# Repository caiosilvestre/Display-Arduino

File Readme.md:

# Sensor de Temperatura com Display
## Projeto Utilizando arduino com Linguagem AVR

## Componentes:
- 1x Display de 4 segmentos.
- 8x Resistores.
- 1x Botão
- Barramento de pinos para acoplamento no arduino.
- 1x LM35.
- 1x Arduino uno.

## Objetivo do Projeto

- Ler o sinal do LM35 
- Converter o sinal em uma escalas de temperaturas
- Utilizar escalas de Temperatura Celsius, Fahrenheit e Kelvin
- Selecionar a escala que será exibida
- Exibir temperatura em tempo real

## Código

Programa requer [arduino.cc](https://www.arduino.cc/).

## Definir ações para as Portas

```sh
#define acende(Y,bit_x)(Y|=(1<<bit_x)) //ativa o bit x da variável Y (coloca em 1)
#define apaga(Y,bit_x)(Y&=~(1<<bit_x)) //limpa o bit x da variável Y (coloca em 0)
#define cpl_bit(Y,bit_x)(Y^=(1<<bit_x)) //troca o estado do bit x da variável Y
#define tst_bit(Y,bit_x)(Y&(1<<bit_x)) //testa o bit x da variável Y (retorna 0 ou 1)
#define BOT PB5
```

## Atribuir valores as variáveis

```sh
const int pinoPOT = A0;
int time = 5, escala = 10, pres = 0;
char  est = 'A';
const int LM35 = A0; // Define o pino que lera a saída do LM35
float temp = 0; // Variável que armazenará a temperatura medida
float VALOR  = 0;
```
## Definir as portas e os valores inicializados
```sh
void setup() {
  int i, s;
  DDRB =  0B00011111;
  DDRD =  0B11111100;
  PORTB = 0B11000001;
  PORTD = 0B11111100;
}
```
## Loop do programa
```sh
    void loop() {
  sete_seg((int)estado_botao());
}
```
## Digitos
- Criada uma matriz com 7 colunas representando os segmentos.
- 1 == HIGH , 0 == LOW.
- Matriz possue 13 linhas, representam um valor a ser exibido no display.
```sh
byte digits[13][7] = {
  { 1, 1, 1, 1, 1, 1, 0 }, // == Digito 0
  { 0, 1, 1, 0, 0, 0, 0 }, // == Digito 1
  { 1, 1, 0, 1, 1, 0, 1 }, // == Digito 2
  { 1, 1, 1, 1, 0, 0, 1 }, // == Digito 3
  { 0, 1, 1, 0, 0, 1, 1 }, // == Digito 4
  { 1, 0, 1, 1, 0, 1, 1 }, // == Digito 5
  { 1, 0, 1, 1, 1, 1, 1 }, // == Digito 6
  { 1, 1, 1, 0, 0, 0, 0 }, // == Digito 7
  { 1, 1, 1, 1, 1, 1, 1 }, // == Digito 8
  { 1, 1, 1, 0, 0, 1, 1 }, // == Digito 9
  { 1, 0, 0, 1, 1, 1, 0 }, // == Letra C
  { 1, 0, 0, 0, 1, 1, 1 }, // == Letra F
  { 1, 1, 1, 0, 1, 1, 1 }, // == Letra A
};  // 
```
## FUNÇÃO EXIBIÇÃO NO DISPLAY 
- Divide o numero inteiro em centena , dezena ,unidade.
- Assim podendo ser exibido de forma separada no display.
```sh
void sete_seg(int num) {
  int cem = (num % 1000) / 100;             /*Parte responsavel por transformar 1 numero em até 3 numeros, centena, Dezena, Unidade*/
  int dez = ((num % 1000) % 100) / 10;
  int uni = (((num % 1000) % 100) % 10);
  escolha_dig(cem);         /*Parte responsavel por determinar em que digito o valor será exibido*/
```
### Parte responsável atribuir cada valor a sua posição no display
- Chamando a função escolha_pos, responsavel por ativar a posição do display.
- Depois da um delay, em seguida chama outra função, responsável transformar o int em portas para display de 7  seguimentos.
```sh
  escolha_pos(0);
  _delay_ms(time);
  escolha_dig(dez);
  escolha_pos(1);
  _delay_ms(time);
  escolha_dig(uni);
  escolha_pos(2);
  _delay_ms(time);
  escolha_dig(escala);
  escolha_pos(3);
  _delay_ms(time);
  escolha_pos(4);
}
```
## Função responsável por selecionar os digitos
- Deixa apenas 1 digito ativo por vez
- Evitando assim exibir valores indesejáveis
```sh
void escolha_pos(int pos) {
  if (pos == 0)
  {
    apaga (PORTB, 1);
    acende(PORTB, 2);
    acende(PORTB, 3);
    acende(PORTB, 4);
  }
  if (pos == 1)
  {
    apaga(PORTB, 2);
    acende(PORTB, 1);
    acende(PORTB, 3);
    acende(PORTB, 4);
  }
  if (pos == 2)
  {
    apaga(PORTB, 3);
    acende(PORTB, 1);
    acende(PORTB, 2);
    acende(PORTB, 4);
  }
  if (pos == 3)
  {
    apaga(PORTB, 4);
    acende(PORTB, 2);
    acende(PORTB, 3);
    acende(PORTB, 1);
  }
}
```
## Traduz o valor int em sinal para o display
```sh
void escolha_dig(int num) {
  int i, j;
  for (i = 0; i < 7; i++)
  {
    if (i == 6 && digits[num][6] == 1)
      acende(PORTB, 0);
    else if (i == 6 && digits[num][6] == 0)
      apaga(PORTB, 0);
    else if (digits[num][i] == 1)
      acende(PORTD, i + 2);
    else
      apaga(PORTD, i + 2);
  }
}
```
## Convert o sinal do lm 35
```sh
float estado_botao()
{
  temp = analogRead(LM35); //RECEBENDO O VALOR INTEIRO
  temp = ((float)temp); // CONVERÇÃO PARA FLOAT
  temp = (temp * 5.0)/1023.0; // CONVERSAO PARA SINAL DE TENSAO
  temp = temp *100; // RESOLVENDO O VALOR
```
## Código para o botão conseguir selecionar a escala desejada
```sh
  switch (est) {
    case 'A':
      if (tst_bit(PINB, BOT))
      {
        pres = 1;
      }
      if (pres == 1 && !tst_bit(PINB, BOT)) {
        est = 'B';//  cesius
        escala = 11;
        pres = 0;
      }
      temp = temp;
      break;
    case 'B':
      if (tst_bit(PINB, BOT))
      {
        pres = 1;
      }
      temp = (temp * 9) / 5 + 32; //  F
      if (pres == 1 && !tst_bit(PINB, BOT)) {
        est = 'C';//  cesius
        escala = 12;
        pres = 0;
      }
      break;
    case 'C':
      if (tst_bit(PINB, BOT))
      {
        pres = 1;

      }
      temp = temp + 273;
      if (pres == 1 && !tst_bit(PINB, BOT)) {
        est = 'A';//  cesius
        escala = 10;
        pres = 0;
      }
      // K
      break;
    default:
      est = 'A';
      break;
  }
  return temp;
}
```

**Free Code!**

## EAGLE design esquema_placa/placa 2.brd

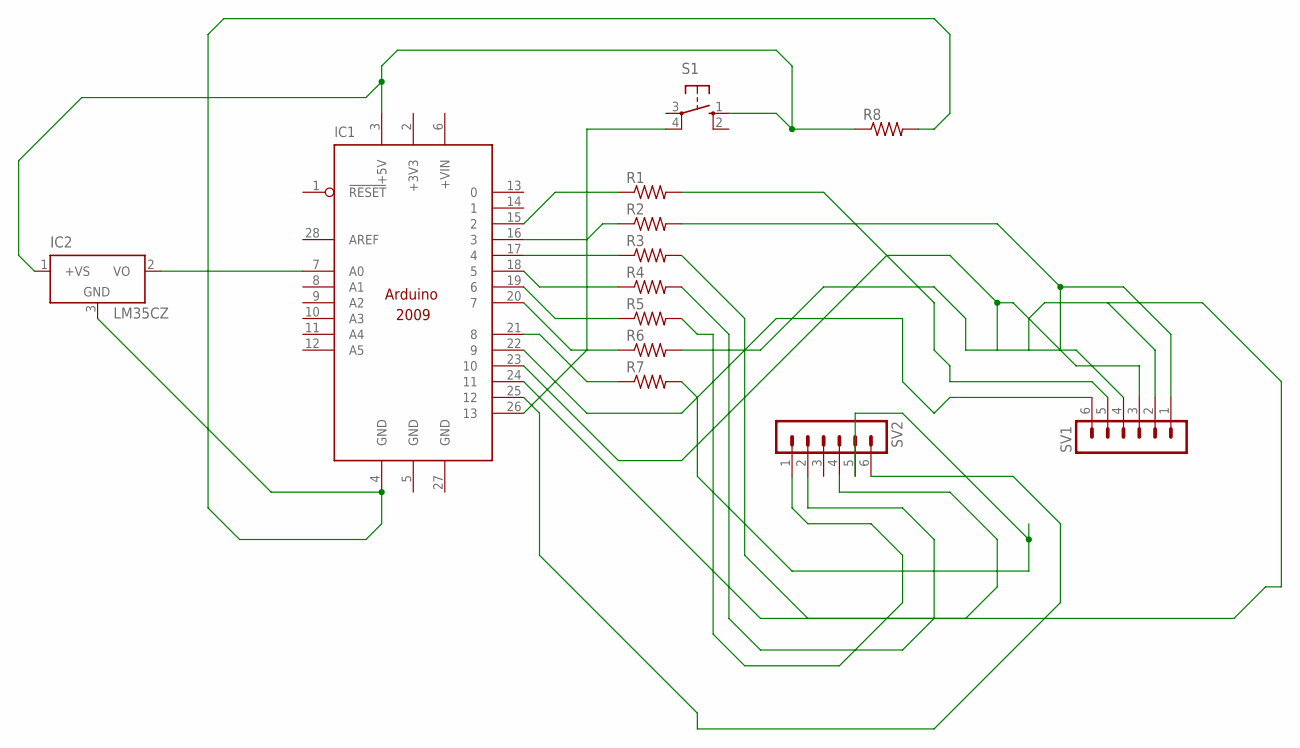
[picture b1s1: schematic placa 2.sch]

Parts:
IC1: ARDUINO2009_11; ARDUINO2009_1
IC2: LM35CZ; TO92
R1, R2, R3, R4, R5, R6, R7, R8: R-US_0207/15; 0207/15
S1: 10-XX; B3F-10XX
SV1, SV2: MA06-1

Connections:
+3V3: IC1.2 (+3V3)
GND: IC1.5 (GND), IC1.27 (GND)
unnamed: IC1.21 (8), R7.1
unnamed: IC1.20 (7), R6.1
unnamed: IC1.19 (6), R5.1
unnamed: IC1.18 (5), R4.1
unnamed: IC1.17 (4), R3.1
unnamed: IC1.16 (3), R2.1
unnamed: IC1.15 (2), R1.1
unnamed: R1.2, SV1.5
unnamed: R2.2, SV1.1
unnamed: R3.2, SV2.4
unnamed: R4.2, SV2.2
unnamed: R5.2, SV2.1
unnamed: R6.2, SV1.4
unnamed: R7.2, SV2.5
unnamed: IC1.22 (9), SV1.6
unnamed: IC1.23 (10), SV1.3
unnamed: IC1.24 (11), SV1.2
unnamed: IC1.25 (12), SV2.6
unnamed: IC1.3 (+5V), IC2.1 (+VS), R8.1, S1.1 (S)
unnamed: IC1.26 (13), S1.4 (P1)
unnamed: IC1.4 (GND), IC2.3 (GND), R8.2
unnamed: IC1.7 (A0), IC2.2 (VO)

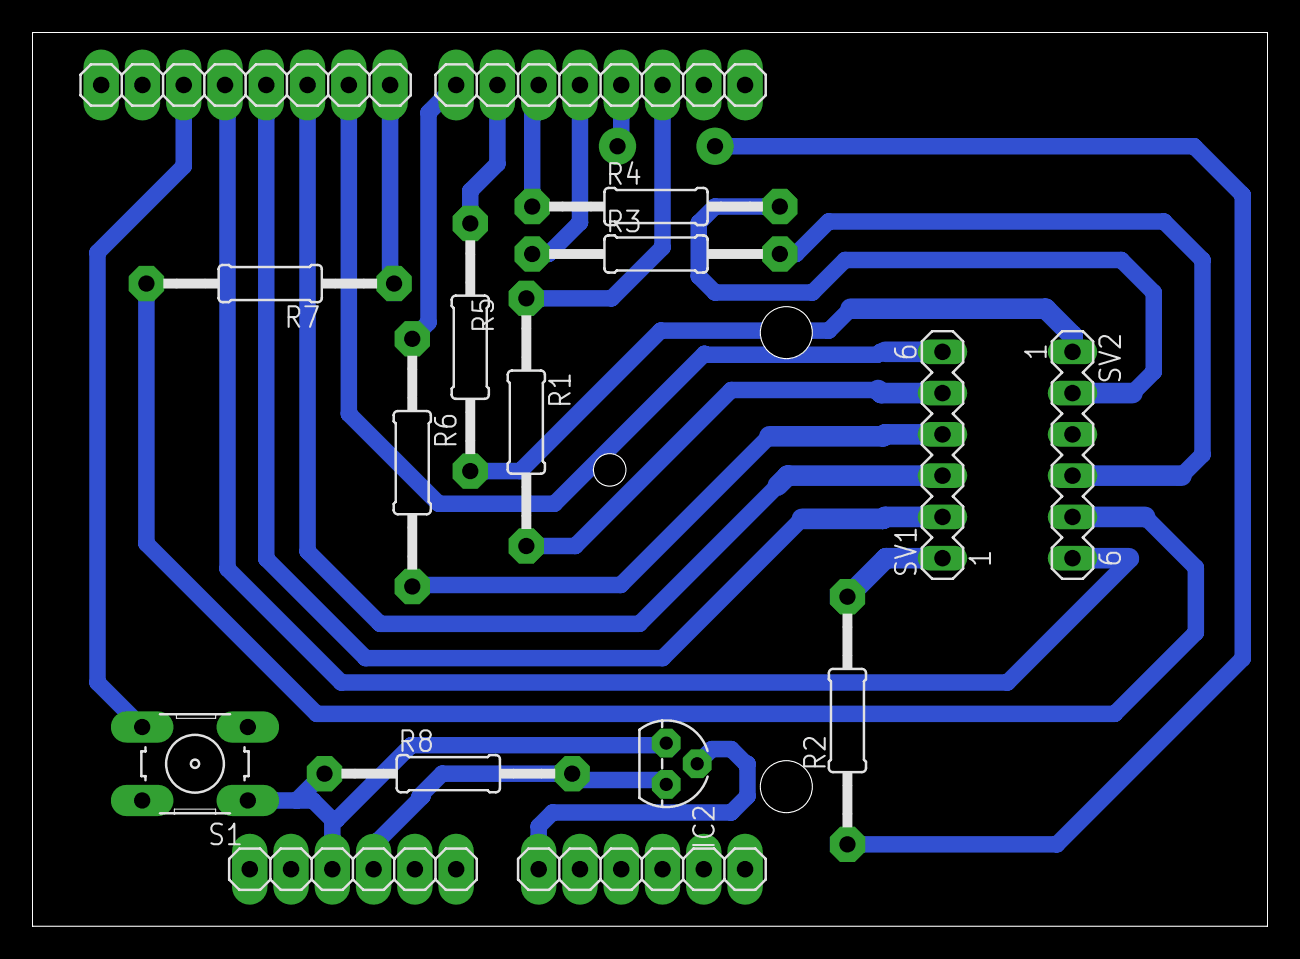
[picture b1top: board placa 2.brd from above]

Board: 2 copper layers, 76.0 x 55.0 mm, 13 parts (0 on the bottom side), 23 nets.

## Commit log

2021-12-21 Explicação do Projeto
2021-12-21 Código do arduino
2021-12-21 Esquema da placa Formato Eagle
2021-12-21 Atualização do Readme.md
    foi adicionado mais fotos do projeto
